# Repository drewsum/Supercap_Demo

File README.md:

# Supercap_Demo
A demo board for a more versatile supercap backup circuit
Based on the LTC4041
PCB and Parts ordered 4/2/2019

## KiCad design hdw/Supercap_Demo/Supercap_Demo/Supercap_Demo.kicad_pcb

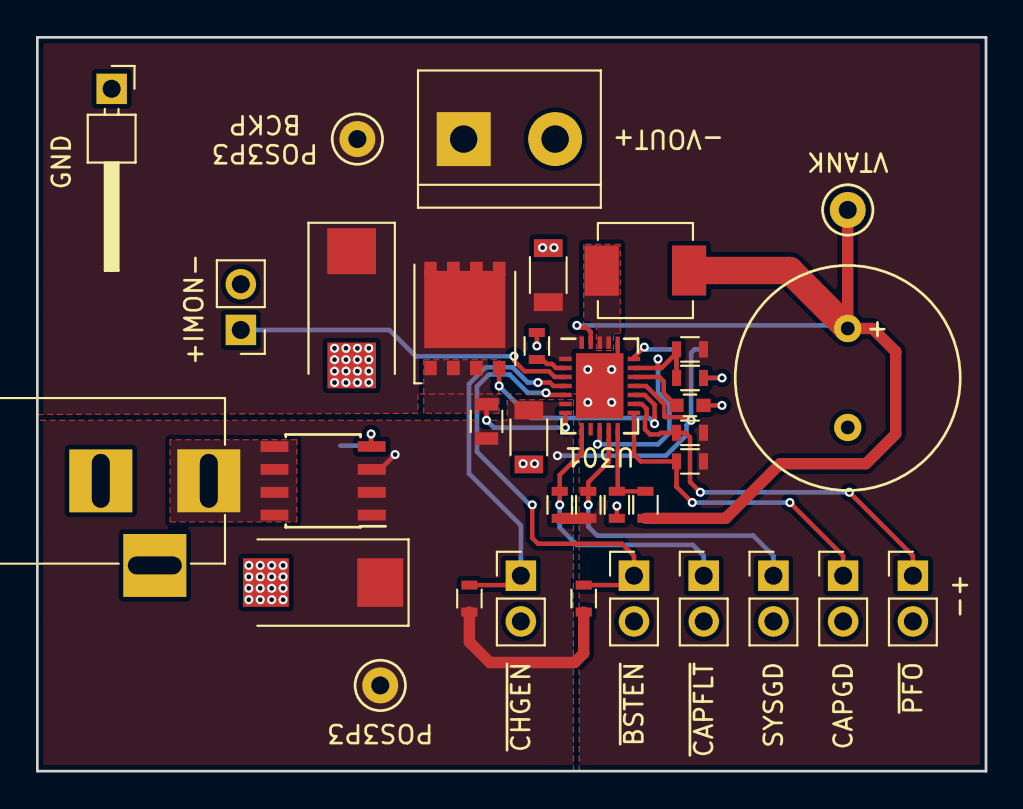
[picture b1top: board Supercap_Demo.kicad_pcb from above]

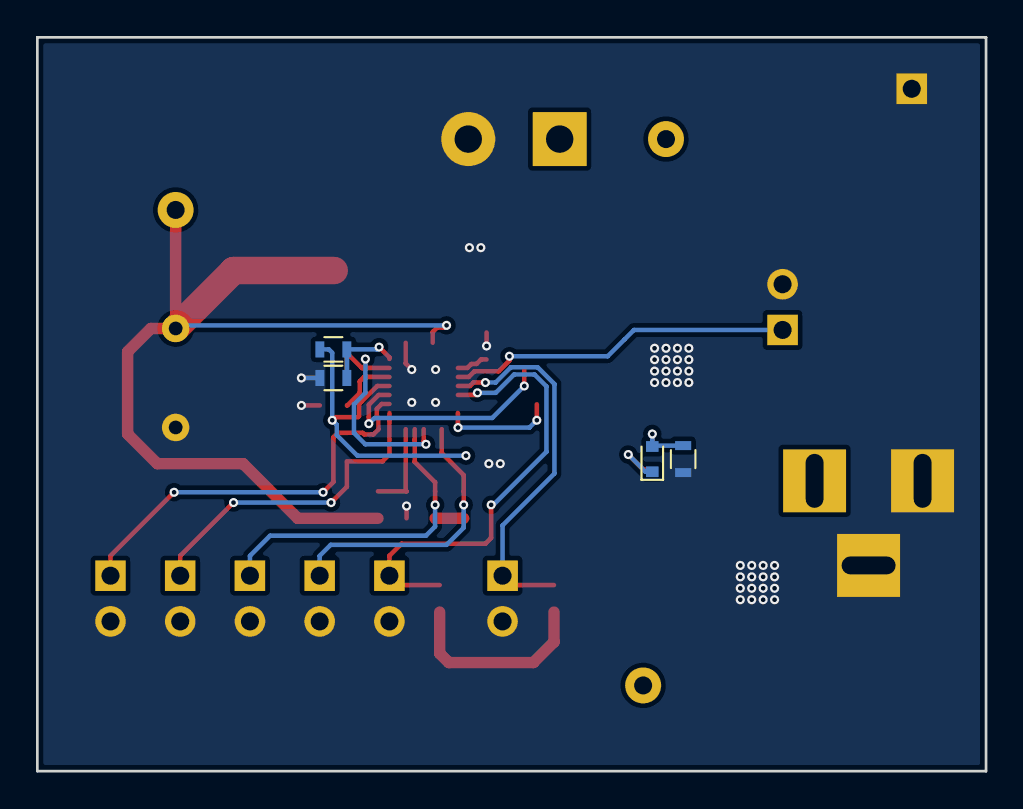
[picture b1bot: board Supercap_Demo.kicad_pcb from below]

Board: 2 copper layers, 52.7 x 40.8 mm, 39 parts (4 on the bottom side), 21 nets.

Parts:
C201, C305: 100uF; CP_Tantalum_Case-D_EIA-7343-31_Reflow
C301, C303: 10uF; C_1206
C302: 2.2nF; C_0603
C304: 15F; SCCT30B156SRB
D201: MM5Z10V; D_SOD-523
J201: +3.3VIN; BARREL_JACK
J202: VOUT; TerminalBlock_bornier-2_P5.08mm
JP301: ~CHGEN; Pin_Header_Straight_1x02_Pitch2.54mm
JP302: ~BSTEN; Pin_Header_Straight_1x02_Pitch2.54mm
L301: 2.2uH; L_Vishay_IHLP-2020
Q201: IRF7404; SOIC-8_3.9x4.9mm_Pitch1.27mm
Q301: IPC100N04S51R7ATMA1; TDSON-8-1
R201: 10k; R_0603
R301, R302, R303, R304, R305, R306: 1M; R_0603
R307: 121k; R_0603
R308: 75k; R_0603
R309: 12m; R_0805
R310: 1k; R_0603
R311: 1.07M; R_0603
R312: 340k; R_0603
R313: 931k; R_0603
R314: 392k; R_0603
TP201: TP; Pin_Header_Angled_1x01_Pitch2.54mm
TP202, TP306, TP307: TP; Test_Point_Keystone_5000-5004_Miniature
TP301: IMON; Pin_Header_Straight_1x02_Pitch2.54mm
TP302: ~CAPFLT; Pin_Header_Straight_1x02_Pitch2.54mm
TP303: CAPGD; Pin_Header_Straight_1x02_Pitch2.54mm
TP304: SYSGD; Pin_Header_Straight_1x02_Pitch2.54mm
TP305: PFO; Pin_Header_Straight_1x02_Pitch2.54mm
U301: LTC4041UFD; QFN-24-1EP_4x5mm_Pitch0.5mm

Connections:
+3.3V_BCKP: C303.1, C305.1, J202.1, Q301.5, R301.1, R302.1, R303.1, R305.1, R311.1, TP306.1, U301.1, U301.24
+3V3: C201.1, C301.1, D201.1, Q201.1, Q201.2, Q201.3, R304.1, R306.1, R307.1, R309.2, TP202.1, U301.6, U301.16
BCKP_CAPGD: R303.2, TP303.1, U301.13
BCKP_IMON: TP301.1, U301.3
BCKP_SYSGD: R302.2, TP304.1, U301.11
GND: C201.2, C301.2, C302.2, C303.2, C304.2, C305.2, J201.2, J201.3, J202.2, JP301.2, JP302.2, R201.2, R308.2, R310.2, R312.2, R314.2, TP201.1, TP301.2, TP302.2, TP303.2, TP304.2, TP305.2, U301.20, U301.25
unnamed: C302.1, U301.17
unnamed: D201.2, Q201.4, R201.1
unnamed: J201.1, Q201.5, Q201.6, Q201.7, Q201.8
unnamed: JP301.1, R304.2, U301.4
unnamed: JP302.1, R306.2, U301.5
unnamed: L301.1, U301.21, U301.22
unnamed: Q301.1, Q301.2, Q301.3, R309.1, U301.7
unnamed: Q301.4, U301.15
unnamed: R307.2, R308.1, U301.19
unnamed: R310.1, U301.2
unnamed: R311.2, R312.1, U301.10, U301.18
unnamed: R313.2, R314.1, U301.12
VTANK: C304.1, L301.2, R313.1, TP307.1, U301.23
~BCKP_CAPFLT: R305.2, TP302.1, U301.8
~BCKP_PFO: R301.2, TP305.1, U301.14

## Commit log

2019-03-08 Made basic kicad project
2019-03-17 Added LTC3129 POS3P3 MNG Circuit
2019-03-23 Finished adding test points, footprints, PNs
2019-03-23 Added BOM
2019-03-23 Started placing parts in PCB
2019-03-23 Placed parts on PCB
2019-04-01 Totaly revised schematic and design, new parts
2019-04-02 Added digikey PNs
2019-04-02 Routed board
